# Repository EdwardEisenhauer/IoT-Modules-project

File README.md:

# IoT-Modules-project
Range, power consumption and data transfer performance tests in OpenThread over STM32WB platform.

## [STM32WB](https://www.st.com/en/microcontrollers-microprocessors/stm32wb-series.html)

The dual-core architecture of the STM32WB enables real-time execution of both application code and network-processing tasks.

### Power Supply

STM32WB require a VDD operating voltage supply between 1.71 V and 3.6 V.

### Clock

### RF 

Micro F Socket UFL

## [OpenThread](https://openthread.io/)

OpenThread is an open-source [Thread](https://www.threadgroup.org/) implementation released by Google.

## Range

## Power consumption

## Data Transfer Performance

I would like to measure the data transfer perfomance, when my device acts as a Router and as an End Device.

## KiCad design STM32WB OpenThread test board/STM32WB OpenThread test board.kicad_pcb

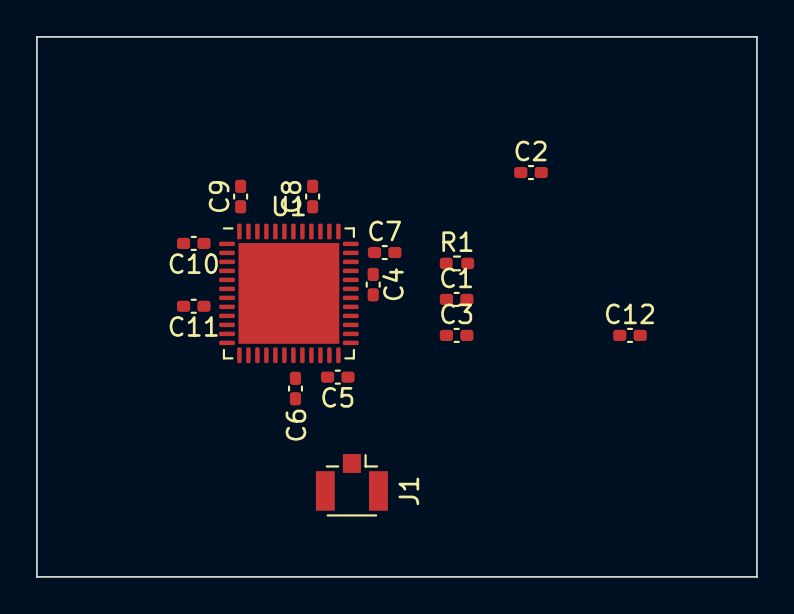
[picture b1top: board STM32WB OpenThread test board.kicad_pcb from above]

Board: 2 copper layers, 40.0 x 30.0 mm, 15 parts (0 on the bottom side), 6 nets, no tracks yet.

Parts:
C1, C2: C; C_0402_1005Metric_Pad0.74x0.62mm_HandSolder
C3, C5, C6, C7, C8, C9, C10, C11, C12: 100n; C_0402_1005Metric_Pad0.74x0.62mm_HandSolder
C4: 4.7u; C_0402_1005Metric_Pad0.74x0.62mm_HandSolder
J1: Conn_Coaxial; U.FL_Hirose_U.FL-R-SMT-1_Vertical
R1: 100k; R_0402_1005Metric_Pad0.72x0.64mm_HandSolder
U1: STM32WB55CC; QFN-48-1EP_7x7mm_P0.5mm_EP5.6x5.6mm

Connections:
GND: C1.1, C2.1, C3.1, C4.1, C5.2, C6.2, C7.2, C8.2, C9.2, C10.2, C11.2, C12.2, J1.2, U1.22, U1.32, U1.49
unnamed: C1.2, U1.25
unnamed: C2.2, U1.24
unnamed: C3.2, R1.2, U1.7
unnamed: C4.2, U1.31
VDD: C5.1, C6.1, C7.1, C8.1, C9.1, C10.1, C11.1, C12.1, R1.1, U1.1, U1.8, U1.20, U1.23, U1.34, U1.35, U1.40, U1.48

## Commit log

2022-03-05 WIP: Introduce KiCAD project
2022-03-10 Introduce MCU
2022-04-02 WIP: Change STM32WB15 for STM32WB55
